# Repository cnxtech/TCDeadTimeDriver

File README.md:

# TCDeadTimeDriver

This repository contains a custom add-on circuit for the [oneTesla v1 Musical Tesla Coil](http://onetesla.com/) to add a Dead-Time between the gate pulses to the IGBT driver transistors to minimize overlap and prevent premature death of the transistors.

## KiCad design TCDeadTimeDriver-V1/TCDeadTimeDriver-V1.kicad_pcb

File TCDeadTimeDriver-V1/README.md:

# Tesla Coil Dead-Time Driver V1 (TCDeadTimeDriver-V1)

Version 1 of the Dead-Time Controller add-on board for the [oneTesla v1 Musical Tesla Coil](http://onetesla.com/).  It is used to add a Dead-Time between the gate pulses to the IGBT driver transistors to minimize overlap and prevent premature death of the transistors.

This board can be ordered from [https://www.oshpark.com/shared_projects/0FoLInjA](https://www.oshpark.com/shared_projects/0FoLInjA).

## Why?

On my oneTesla coil, I have been fighting some issues of "shoot-thru" in the half-bridge driver that causes both transistors to conduct and short, blowing both transistors and the fuse and sometimes frying the resistor on the gates and other carnage.

So, I designed this little add-on. It has greatly helped by allowing for an adjustable dead-time between the pulses to the half-bridge. The circuit uses two chips and fits in series between pin 4 of the 74HCT14 and pin 2 of each of the UCC2732x driver chips on the original oneTesla v1 main board. You do have to swap-out the UCC27321 for a second UCC27322 as this circuit needs two non-inverting drivers instead of one inverting and one non-inverting.

I'm posting it here for others who have had similar issues. It doesn't fully solve all failure modes possible, but definitely helps.

## Tools needed:

- Oscilloscope with at least two channels and delta-T markers
- Signal generator capable of producing either a +5V TTL signal or a +/- 5V (or so) AC sinewave in the 200-300kHz range
- Frequency counter.
- oneTesla v1 Musical Tesla Coil (assembled)

## To use and calibrate:

1. First, use the original circuit as-is with a scope on pin 4 of the 74HCT14 on the oneTesla main board to find the frequency of the primary circuit with the coil running generating high-voltage (Warning: Care must be exercised to isolate test equipment and keep output power minimal!!). This has to be done using the delta-T markers on the scope instead of a frequency counter because the interrupter will not have the coil running continously (and you wouldn't want to be that close to it measuring frequencies if it was). You have to trigger the scope at the right spot and crank up the intensity of the beam to handle the rescans necessary to see it (i.e. it will be dim) on analog scopes. On digital scopes, you may be able to program it to simply record the correct spot of the wave (I'm old school and tend to prefer using analog scopes, even though I own both). For reference, mine measured 286 kHz.

2. Build and Connect this add-on TCDeadTimeDriver circuit between pin 4 of the 74HCT14 and pin 2 of each of the UCC2732x driver chips, replacing the xx321 driver with a xx322 driver. This new circuit needs two NON-inverting drivers to function. The original oneTesla design has one inverting and one non-inverting. So you have to use two UCC27322 chips instead. You'll need to either cut traces or pull the pins out of the sockets and solder a short lead to connect them, as the original circuit has both pin 2s of the drivers together. This circuit needs them separated so they can connect to the two independent outputs of the SG3525. And you must disconnect the existing route of pin 4 of the 74HCT14 that's currently going to pin 2 on both drivers, as that pin must go to this circuit first and not to the drivers. Note: The output of pin 4 of the 74HCT14 must continue to connect to the clock input of the 74HCT74 so you do not want to pull its pin out of the socket. Instead, solder on a wire either at the feed-through pad that's on one of the trace-routes on the board or simply solder it to the pin with the pin still inserted in its socket, which is what I did.

3. Power-up ONLY the low-voltage circuitry and put a dual-trace scope on Out#1 and Out#2 on this add-on board, which are pins 11 and 14 of the SG3525 (or pin 2 of each of the drivers). Adjust the dead-time potentiometer (pin 7 of the SG3525) to set the desired pulse separation for the drivers, but don't go too wide with the separation or you'll run out of bandwidth on the SG3525, as it's only rated for 400kHz for the oscillator (which must run at twice the resonant frequency of the primary winding). Note: If you set it too wide, you'll find out in the next step as you won't be able to set the desired frequency without the SG3525 outputs going "Minnie-Mouse" on you. If you later want to change the dead-time, you must also readjust your frequency in the next step as the dead-time pot affects it too. Even at the minimum setting, you'll get a nice dead-time added. The exact range of dead-time you can get depends on the exact frequency you are running. For reference, my circuit (running at 286 kHz) is adjustable from 266nS to 792nS. I'm actually still running mine at around 266nS, which is significantly more than the original oneTesla circuit, which only had the propagation delay of the drivers to add dead-time.

4. Adjust the frequency set potentiometer (pin 6 of the SG3525) until the frequency is about 5% lower than the target resonant frequency of the primary. For example, I tuned mine to 270 kHz for a resonant of 286 kHz (meaning the two outputs, pins 11 and 14 of the SG3525, should indicate 286 kHz on the frequency counter and pin 4 (the Freq Out test point) of the SG3525 should read about 540 kHz, yes it exceeds the 400 kHz published limit of the SG3525, but it still works well. My chip actually functioned correctly all the way to the mid-600 kHz range, though the higher it is, the less adjustment you'll have on the dead-time control).

5. Hook a signal generator to the current sense transformer conditioning circuit on either side of the 0.1uF cap that leads into pin 1 of the 74HCT14 on the oneTesla main-board (depending on the type of signal you are generating -- one side needs a sine-wave, the other can use a square wave)...

6. Set the frequency on the signal generator for the resonant frequency measured in Step #1. Verify a corresponding signal on pin 4 of the 74HCT14. It should be a nice square-wave at your resonant frequency.

7. Use a dual-trace scope to display one of the two outputs of the SG3525 (either pin 14 or 11) and pin 3 of the SG3525 (or pin 13 of the 74LS123), which is the sync signal and will be the 2x clock source to do a phase-locked-loop on the SG3525 so that it creates the same frequency as the resonant of the primary. You should now see the SG3525 output pins resyncing in conjunction with the pulse coming into pin 3, causing the frequency on pins 14 and 11 of the SG3525 to shift accordingly, forming a simple phase-locked-loop circuit.

8. Adjust the sync-pulse width potentiometer (pin 15 of the 74LS123) until the SG3525 is able to correctly lock onto the same frequency as the signal generator is supplying. You should find that there's a band in the adjustment range of the sync pulse-width where it will pull-in to the correct frequency and lock to it. Adjust it to the middle of this adjustment band so that there's ample tolerance on either side in case the frequency drifts slightly.

9. That's it... Disconnect the test equipment, and use the coil as before...

With this circuit, I've been blowing far fewer transistors than before. If calibrated correctly, output power should be the same, if not better than without it. And if you needed to remove it for some reason, you can simply disconnect this board and jumper the pin 2 of the drivers back to their original connection point and replace the non-inverting driver with the original inverting version.

Also, I've found that 3-position Phoenix Contact connectors (normally used for attaching wires to a circuit board) will fit the transistor holes and allow a method to "socket" the IGBT transistors on the oneTesla main-board. After the 5th or 6th time of unsoldering and resoldering the transistors (a delicate, time-consuming task), I switched to that and now I can change the transistors without even removing the circuit board. Though with this circuit addition, I haven't needed to do so quite as often. :-)

### Bill of Materials:

- C1 : 220pF Ceramic
- C2 : 220pF Ceramic
- C3 : 22pF Ceramic
- C4 : 0.001uF Mica
- C5 : 0.1uF Mylar
- C6 : 0.1uF Mylar
- C7 : 0.01uF Ceramic
- C8 : 10uF 25V Electrolytic
- C9 : 10uF 25V Electrolytic
- C10 : 0.01uF Ceramic
- C11 : 0.01uF Ceramic
- D1 : 1N4148
- D2 : 1N4148
- R1 : 470 Ohm 1/4W
- R2 : 470 Ohm 1/4W
- R3 : 20K Ohm Multiturn Potentiometer
- R4 : 1K Ohm 1/4W
- R5 : 2K Ohm Multiturn Potentiometer (see fine-tuning notes below)
- R6 : 1K Ohm 1/4W (see fine-tuning notes below)
- R7 : 100 Ohm Multiturn Potentiometer
- P1 : Molex 4-Pin Header connector (0022232041) DigiKey: WM4202-ND
- P1 Mate : Molex 4-Pin Female Receptacle (0022013047) DigiKey: WM2002-ND
- P2 : Molex 3-Pin Header connector (0022232031) DigiKey: WM4201-ND
- P2 Mate : Molex 3-Pin Female Receptacle (0022013037) DigiKey: WM2001-ND
- Pins for P1 and P2 : Molex Female Crimp Pin (0008500113) DigiKey: WM1114CT-ND
- 2x 16-pin dip sockets
- U1 : 74LS123 IC (16-pin dip)
- U2 : SG3525 IC (16-pin dip)
- second UCC27322 to replace the UCC27321 on the oneTesla main board

(Note: it may work OK with a 74HCT123, but the specs on it are a bit different than the 74LS123 and I haven't tried it. I've only used the LS family part, since I happened to have one on-hand already)... So you'll have to experiment. Maybe someone can test that and post their results?

Also, you may can get away with a mylar cap for the 0.001uF timing capacitor. But it will have worse frequency drift than a mica part. As long as it stays within the 5-10% window of tolerance for the SG3525 sync logic, it should work. The mica cap is definitely better and I happened to have one on-hand, so that's what I used.

## Why the need to switch to two (non-inverting) UCC27322 drivers?

The requirement of two non-inverting drivers shouldn't be a mystery. The oneTesla Coil uses a half-bridge to drive the primary winding. The half-bridge uses two transistors to alternately drive one side of the coil to V+ and ground (one transistor takes it to V+ and the other to ground), meaning that only one of the two transistors can be turned on at a time.

In the original design, they used the square-wave output from the current sense circuit to go to the input of both driver chips and they had one inverting driver and one non-inverting driver. The non-inverting drver turned one transistor on when the square-wave was high and the inverting driver turned the other transistor on when the square-wave was low. This allowed it to toggle between the two transistors turning only one on at a time.

The problem is that transistors turn on quicker than they turn off. This means that there's a slight overlap between the on and off cycles if there isn't a slight delay between switching which transistor is turned on. If both transistors turn on simultaneously, then you have V+, which in this case is the rectified direct AC mains voltage, shorted directly to ground, a problem known as "shoot-through". That causes the transistors to fail.

Short bursts you can get away with, but it produces a lot of heat (and reduces operating efficiency and overall power in the coil) and if the overlap gets slightly longer, which can happen because they get even slower as they get hotter, then eventually --- boom! The transistors short out completely and die...

The only delay between the pulses in the original circuit design was the propagation time through the driver chips and gate drive transformer, plus the capacitance of the gates of the transistors (i.e. their charge/discharge time). Granted, the IGBT's used in the oneTesla driver design has pretty fast on and off times and nearly symmetric on/off times, which is what mostly kept them out of trouble. But still, if you load up the Tesla Coil a bit to where there is more current draw through the transistors, the switch-on vs. switch-off time differential will worsen, and they will eventually fail... And that's why I made this circuit.

The SG3525 requires a clock that's twice the frequency of the outputs its driving, so that it can use one cycle to turn on one output (one transistor) and the other cycle to turn on the other output (other transistor), completely independently. So, I used the 74LS123 circuit as a frequency doubler to double the square wave from the current sense transformer -- giving a short pulse at the beginning of both the high-period and low-period of the original circuit signal. That gets feed to the SG3525's sync input to clock it and phase lock it to the current sense transformer (and lock it to the resonant frequency of the primary winding of the Tesla Coil in the process).

The SG3525 has two outputs that can either go to a driver or straight to the transistors (depending on your circuit and needs). But the outputs are both high-going pulses for on. That means that you can't invert one of them before sending it to the transistor or you'll end up turning on both transistors at the same time (very bad). So you have to use two non-inverting drivers. That way each transistor is turned on only when it should.

And they have to be non-inverting because the SG3525 is setup to drive the outputs high for on and low for off. There's a SG3527 with them inverted. And on it, you'd need both to be inverting drivers to invert them back to the correct polarity before going to the transistors. Essentially the SG3525 is designed for driving N-channel devices (as these transistors are) and the SG3527 is designed for driving P-channel devices.

The SG3525 has a circuit that lets you use a resistor or potentiometer to set a delay time between the two output pulses, known as the dead-time. During this time, both outputs are off, allowing time for the one transistor to turn off completely before turning on the other. That was my whole reason for adding this circuit as it gave me a way of dialing in a precise nanosecond delay between switching transistors.

In my opinion, this "add-on" isn't really optional. They are just barely getting away with things in the original circuit design and if you need to switch to a different transistor, such as one able to switch higher voltage or current (as I have also been experimenting with), well, they tend to have even longer turn-off times (with a nearly same fast turn on time) which only exacerbates the problem even more.

I originally experimented with other tricks of adding dead-time. But they were all sub par in one way or another. For example, I tried things like a larger gate resistor with a diode so that the on-time gate charge time would be longer than the off-time gate discharge time to bring the on and off times back to being more symmetrical with one another. But that caused problems with the startup or "ring up" operation of the primary and tended to cause it to not want to start oscillating.

There were some other failed attempts to do similar tricks with the pulses in the current sense transformer buffer circuit. While I got several configurations to function, they were still too picky about the specific component values and exact operating conditions of the coil. So I finally punted and designed this proper circuit for it.

## Fine-tuning values to match your coil...

The values specified in the original Dead-Time Add-on Circuit worked well for my original coil configuration.  But after I made some modifications, like adding a strike-ring and a special ground-plane, I found that the resonant frequency of my secondary had dropped nearly 7% from what it was, from 246.5.kHz with a simulated streamer (284kHz or so without the simulated streamer) down to 230kHz (260kHz without the simulated streamer).

In my original "out-of-the-box" configuration, my primary resonance (which was found to be 286kHz) was really close to my secondary without the simulated streamer, but was 16% higher than the secondary with the simulated streamer.  Now, typically you'd tune them intentionally out-of-tune slightly, but generally the other way around -- making the primary a little lower than the secondary so that when streamers form (especially ones that strike a ground) and pulls down the resonant frequency of the secondary, it moves more in-tune with the primary than out.

Nonetheless, my original experimentation was with the out-of-the-box setup with the coil built as-per the instructions.  And so my original Dead-Time circuit was optimized for a 286kHz primary frequency.  But now that I've made some physical changes and caused them to be a bit out-of-tune in general, I'm looking at modifying the tank capacitor and/or winding of the primary to correct my tuning issues.

What I'm finding is that the original component selection on my Dead-Time Add-On circuit is inadequate for the potentiometer R5 (2K) and fixed-resistor R6 (1K) values  in selecting the proper frequency.

One solution is to change the potentiometer R5 from 2K to 5K.  That should give you all of the adjustment range you'll ever need.  However, you will sacrifice accuracy of fine-tuning adjustment.  Therefore, you may opt to change the fixed-resistor R6 instead, which is my choice.

Here's a little chart showing common fixed-resistor values for R6 with the original 2K adjustment potentiometer R5:

<table><tr><td></td><td>|</td><td>Zero Dead</td><td></td><td>|</td><td>Max Dead</td><td></td><td>|</td><td>Working Range</td><td></td><td>|</td><td>Effective Range</td><td></td></tr>
<tr><td>Rfixed</td><td>|</td><td>FreqMin</td><td>FreqMax</td><td>|</td><td>FreqMin</td><td>FreqMax</td><td>|</td><td>FreqMin</td><td>FreqMax</td><td>|</td><td>FreqMin</td><td>FreqMax</td></tr>
<tr><td>2700</td><td>|</td><td>151976</td><td>264550</td><td>|</td><td>139276</td><td>228311</td><td>|</td><td>151976</td><td>228311</td><td>|</td><td>151976</td><td>205479</td></tr>
<tr><td>2400</td><td>|</td><td>162338</td><td>297619</td><td>|</td><td>147929</td><td>252525</td><td>|</td><td>162338</td><td>252525</td><td>|</td><td>162338</td><td>227273</td></tr>
<tr><td>2200</td><td>|</td><td>170068</td><td>324675</td><td>|</td><td>154321</td><td>271739</td><td>|</td><td>170068</td><td>271739</td><td>|</td><td>170068</td><td>244565</td></tr>
<tr><td>2000</td><td>|</td><td>178571</td><td>357143</td><td>|</td><td>161290</td><td>294118</td><td>|</td><td>178571</td><td>294118</td><td>|</td><td>178571</td><td>264706</td></tr>
<tr><td>1800</td><td>|</td><td>187970</td><td>396825</td><td>|</td><td>168919</td><td>320513</td><td>|</td><td>187970</td><td>320513</td><td>|</td><td>187970</td><td>288462</td></tr>
<tr><td>1500</td><td>|</td><td>204082</td><td>476190</td><td>|</td><td>181818</td><td>370370</td><td>|</td><td>204082</td><td>370370</td><td>|</td><td>204082</td><td>333333</td></tr>
<tr><td>1200</td><td>|</td><td>223214</td><td>595238</td><td>|</td><td>196850</td><td>438596</td><td>|</td><td>223214</td><td>438596</td><td>|</td><td>223214</td><td>394737</td></tr>
<tr><td>1000</td><td>|</td><td>238095</td><td>714286</td><td>|</td><td>208333</td><td>500000</td><td>|</td><td>238095</td><td>500000</td><td>|</td><td>238095</td><td>450000</td></tr></table>

I've shown the frequency range for both minimum and maximum dead-time adjustment.  The Working Range column shows the minimum and maximum frequency for the full-span of the dead-time adjustment (that is the maximum minimum-frequency and the minimum maximum-frequency).  And the last column, labeled Effective Range, is the same as the Working Range, but has the maximum frequency scaled down by 10%, as I've found in nearly every situation that the real frequency is about 10% less than that calculated by the SG3525 timing equations.  So that's the column you should use.

I'm sure this 10% degradation of frequency is a composite of the tolerance in the involved components as well as the SG3525 equation being only an approximation.  The minimum would similarly be scaled down by 10%, but I left it unchanged as only the tighter range should be considered the real working range.  Though, I've never seen it be off in the other direction with higher frequencies than those predicted, only lower frequencies.

On my circuit, I am changing R6 from 1K to something closer to 2K to allow me to target the new resonant frequency of my primary and to still allow for a nice range of adjustment without giving up fine-tuning ability on the potentiometer.

I also highly recommend the JavaTC applet found on [http://www.classictesla.com/](http://www.classictesla.com/).  I have found it to not only be extremely useful, but quite accurate as well, assuming you are careful in measuring things and entering correct dimensions and values.  In fact, when I entered the data for my coil, its predicted resonant frequency for both the primary and secondary was only off by a few kilohertz.

The only value I question on JavaTC is the DC Resistance of the secondary.  On mine, I measure 250.7-ohms.  But it predicted 511-ohms, which is nearly a perfect factor of 2, and makes me wonder if they are simply missing a divide by two in their model.  But otherwise, I found everything to be nearly exact -- that is, once I entered all of the new modifications I made to my coil, such as the strike-ring and ground plane positions and dimensions.

## Comparison Videos with and without this circuit

One evening while working on the tuning of my coil, I opted to disconnect and remove my Dead-Time Circuit and just get it out of the way temporarily so I wouldn't have to worry about recalibrating it while tuning the coil. This is easy to do on my setup because I put little molex header connectors on it rather than hardwiring things.

After several rounds of working with the coil tuning, I opted to play a song on it via MIDI and decided to give it a go without the Dead-Time Circuit installed. A little over a minute into the song and there's the infamous flash of green light of the fuse blowing as the transistors die. I was playing "Amazing Grace", but am thinking I should have played "Another One Bites the Dust" instead, as my pile of dead transistors continues to grow.

I then replaced the transistors and fuse and swapped the Dead-Time Circuit back in and recalibrated it for the frequency of the coil. And then immediately played "Amazing Grace" again without changing any other settings.

I've made the videos from those tests available for you to see so you can compare them and see how the coil behaves with and without the Dead-Time Circuit installed. As I mentioned above, if the circuit is properly calibrated, you'll not notice any performance differences other than your transistors won't die when running long pulse widths and higher powers. So I think this is a good demo of why I designed this circuit in the first place. It's amazing how much it helps just removing that little bit of overlap with a little Dead-Time.

Here's the links to the videos:

- [Amazing Grace without the Dead Time Circuit](http://cloud.dewtronics.com/videos/oneTesla_201503070003_AmazingGrace_without_DeadTimeCkt_360p.mp4)

- [Amazing Grace with the Dead Time Circuit](http://cloud.dewtronics.com/videos/oneTesla_201503070141_AmazingGrace_with_DeadTimeCkt_360p.mp4)

## Setting Sync Pulse Width Adjustment for a Frequency Range

Overall, I have been pleased with the functionality of the dead-time circuit.  In fact, I've found in my calibrating of it, that you can actually dial in a whole range of frequencies that it will phase-lock to rather than targeting a specific frequency as I describe above, even though it technically only has to ever lock into the resonant frequency of the primary itself.

To do that, hook the SG3525 output to a scope and frequency counter and turn on the low-voltage/logic power (no high voltage).   First set your desired dead-time width, as that adjustment affects the overall frequency and signal locking characteristics.  I'm still running on the lowest setting on dead-time on this coil.  Next, you set the desired lowest frequency you want it to be able to lock to using the frequency set pot, as can be noted on your frequency counter.  This value should probably be based on the resonant frequency of the coil with a simulated streamer, as that feels like the best value to use.

Next, turn down the sync pulse width (increased resistance on that pot if my memory is correct) and apply a frequency with a frequency generator to the current sense transformer circuit, start with the same frequency you dialed into the frequency set pot.  Then gradually crank up the frequency on the signal generator to the desired highest frequency of the range you wish it to lock, turning up the sync pulse width pot as you increase the frequency to the point that the SG3525 locks to that new frequency.  Or to do it quicker, you could just crank up the signal generator to the highest frequency you want to lock and turn the sync pulse width pot until it locks.

At that point, you should be able to sweep the frequency on the signal generator anywhere between the low frequency set point and the higher frequency set point and the SG3525 should lock to it, only losing lock when you exceed that range on either side.  I'm not sure the SG3525 was designed to operate as a phase locked loop, but it performs admirably as one for these frequencies.

I don't know how big of an overall range it's able to lock, but in the video linked above, mine was calibrated to lock the range of about 250kHz to 300kHz.  The primary, still with the original 0.068uF cap, is running around 287kHz as its resonant.  The resonant of my secondary, without simulated streamers is 260kHz.  With a simulated streamer it's around 225-230kHz.  Once I get my hands on a 0.083uF cap (since my coil is still not properly tuned yet), I believe it will be nearly perfectly tuned and I should be able to change my lock range to something more like 230kHz to 280kHz.

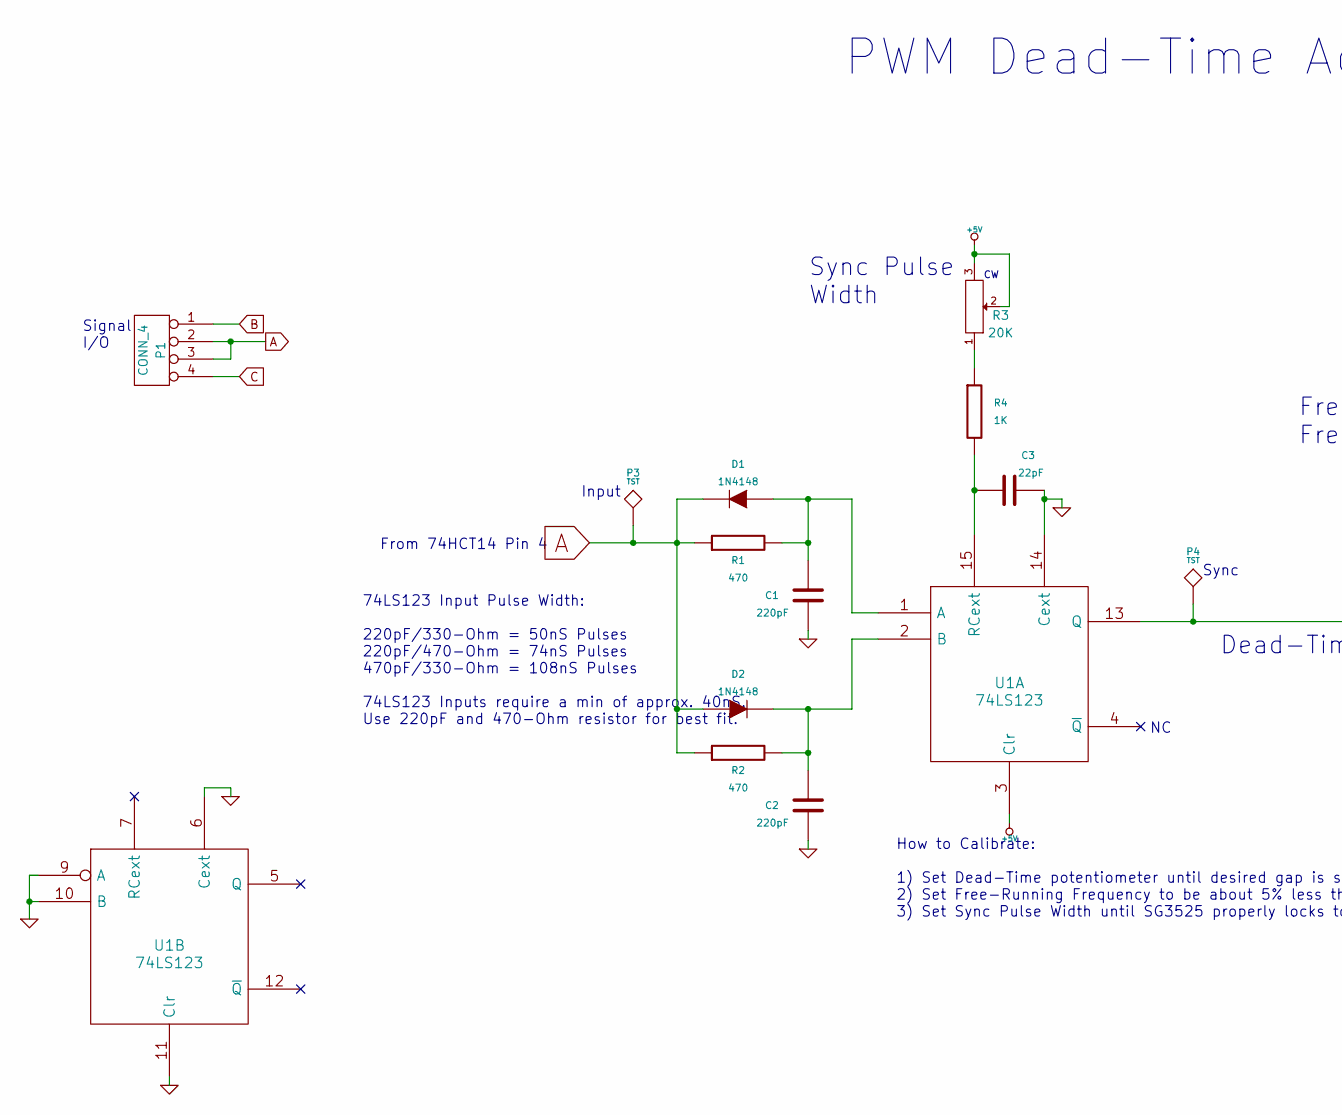
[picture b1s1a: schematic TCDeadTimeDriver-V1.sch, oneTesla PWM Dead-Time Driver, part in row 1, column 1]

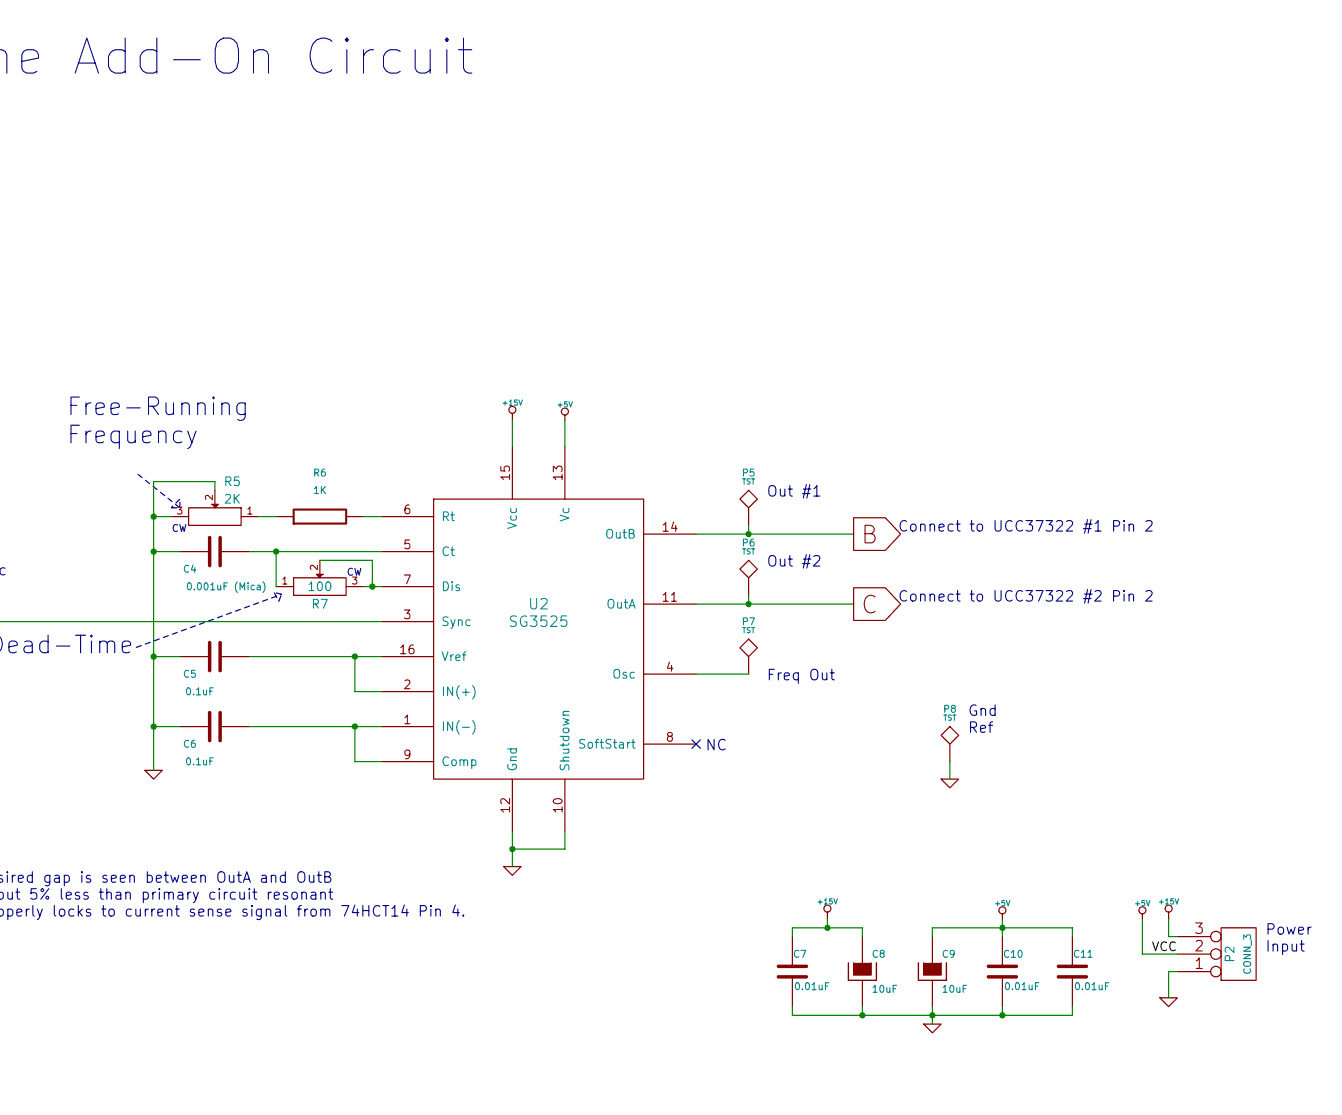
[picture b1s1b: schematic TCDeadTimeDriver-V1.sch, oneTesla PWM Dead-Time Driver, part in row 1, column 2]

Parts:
C1, C2: 220pF
C3: 22pF
C4: 0.001uF (Mica)
C5, C6: 0.1uF
C7, C10, C11: 0.01uF
C8, C9: 10uF
D1, D2: 1N4148
P1: CONN_4
P2: CONN_3
P3, P4, P5, P6, P7, P8: TST
R1, R2: 470
R3: 20K
R4, R6: 1K
R5: 2K
R7: 100
U1: 74LS123
U2: SG3525

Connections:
+5V: C9.1, C10.1, C11.1, P2.2 (PM), R3.2, R3.3, U1.3 (Clr), U1.16 (VCC), U2.13 (Vc)
+15V: C7.1, C8.1, P2.3, U2.15 (Vcc)
A: D1.2 (K), D2.1 (A), P1.2, P1.3, P3.1, R1.1, R2.1
B: P1.1, P5.1, U2.14 (OutB)
C: P1.4, P6.1, U2.11 (OutA)
GND: C1.2, C2.2, C3.2, C4.1, C5.1, C6.1, C7.2, C8.2, C9.2, C10.2, C11.2, P2.1, P8.1, R5.2, R5.3, U1.6 (Cext), U1.8 (GND), U1.9 (A), U1.10 (B), U1.11 (Clr), U1.14 (Cext), U2.10 (Shutdown), U2.12 (Gnd)
unnamed: R6.2, U2.6 (Rt)
unnamed: R5.1, R6.1
unnamed: C4.2, R7.1, U2.5 (Ct)
unnamed: R3.1, R4.1
unnamed: C6.2, U2.1 (IN(-)), U2.9 (Comp)
unnamed: C5.2, U2.2 (IN(+)), U2.16 (Vref)
unnamed: P4.1, U1.13 (Q), U2.3 (Sync)
unnamed: C2.1, D2.2 (K), R2.2, U1.2 (B)
unnamed: C1.1, D1.1 (A), R1.2, U1.1 (A)
unnamed: P7.1, U2.4 (Osc)
unnamed: R7.2, R7.3, U2.7 (Dis)
unnamed: C3.1, R4.2, U1.15 (RCext)

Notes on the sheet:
Sync Pulse Width
Free-Running Frequency
Dead-Time
74LS123 Input Pulse Width: 220pF/330-Ohm = 50nS Pulses 220pF/470-Ohm = 74nS Pulses 470pF/330-Ohm = 108nS Pulses 74LS123 Inputs require a min of approx. 40nS. Use 220pF and 470-Ohm resistor for best fit.
Freq Out
From 74HCT14 Pin 4
Connect to UCC37322 #1 Pin 2
Connect to UCC37322 #2 Pin 2
PWM Dead-Time Add-On Circuit
How to Calibrate: 1) Set Dead-Time potentiometer until desired gap is seen between OutA and OutB 2) Set Free-Running Frequency to be about 5% less than primary circuit resonant 3) Set Sync Pulse Width until SG3525 properly locks to current sense signal from 74HCT14 Pin 4.
Power Input
Signal I/O
Sync
Input
Out #1
Out #2
Gnd Ref

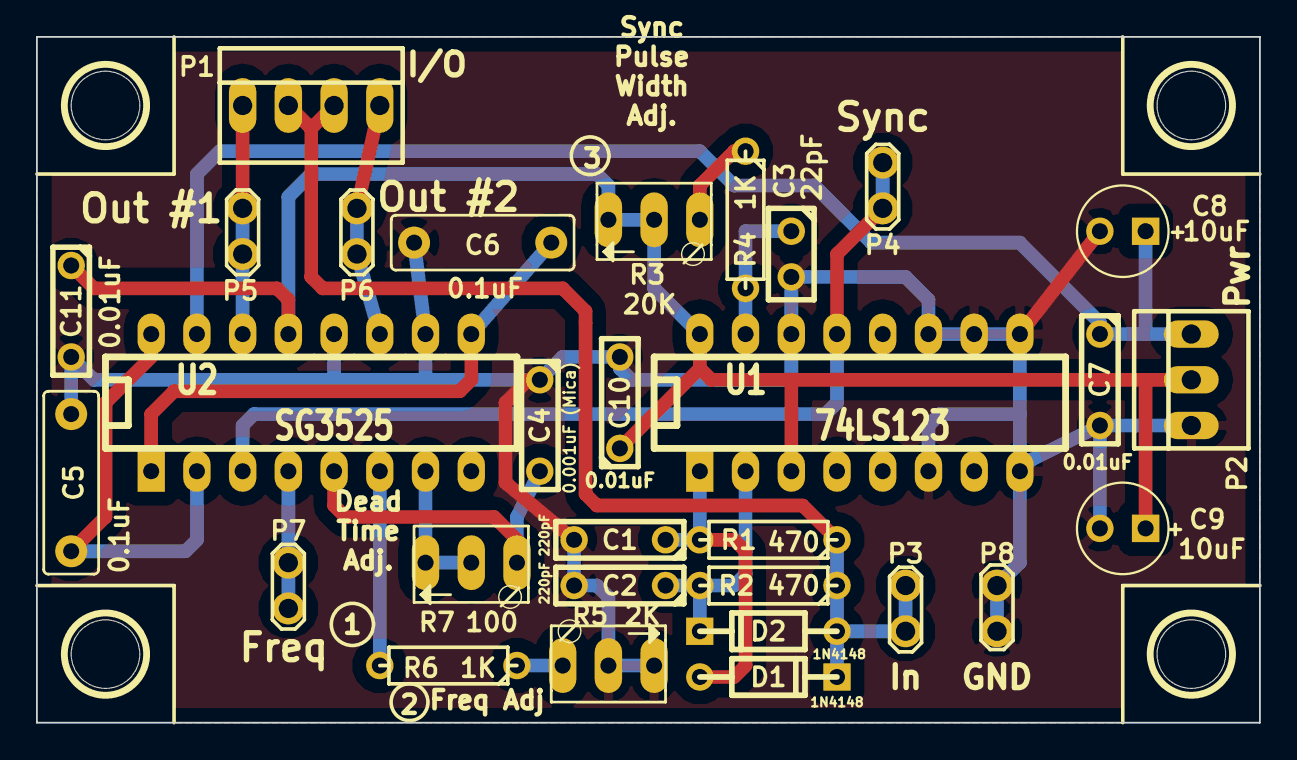
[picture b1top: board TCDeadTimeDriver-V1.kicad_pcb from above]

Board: 2 copper layers, 67.9 x 38.1 mm, 34 parts (0 on the bottom side), 18 nets.

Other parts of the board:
1PIN, 1PIN#2, 1PIN#3, 1PIN#4: P***; 1pin

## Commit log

2016-12-17 Official V1 release of the Tesla Coil Dead-Time Driver V1 Board.
2016-12-17 Updated README for TCDeadTimeDriver-V1.
2016-12-17 Fixed formatting in README for TCDeadTimeDriver-V1
2016-12-18 Updated README from oneTesla notes and postings.
2016-12-18 Fixed table markdown in README.
    The online markdown instructions for tables just doesn't work. Only recourse was to use inline html.

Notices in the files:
TCDeadTimeDriver-V1/TCDeadTimeDriver-V1.kicad_pcb:
Copyright(c)Dewtronics
